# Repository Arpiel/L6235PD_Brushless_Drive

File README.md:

# L6235PD_Brushless_Drive
L6235PD BLDC Drive Project

3 Phase brushless Drive using L6235PDTR

Using Tool:KiCad 7.0

L6235 datasheet:https://www.st.com/resource/en/datasheet/l6235.pdf

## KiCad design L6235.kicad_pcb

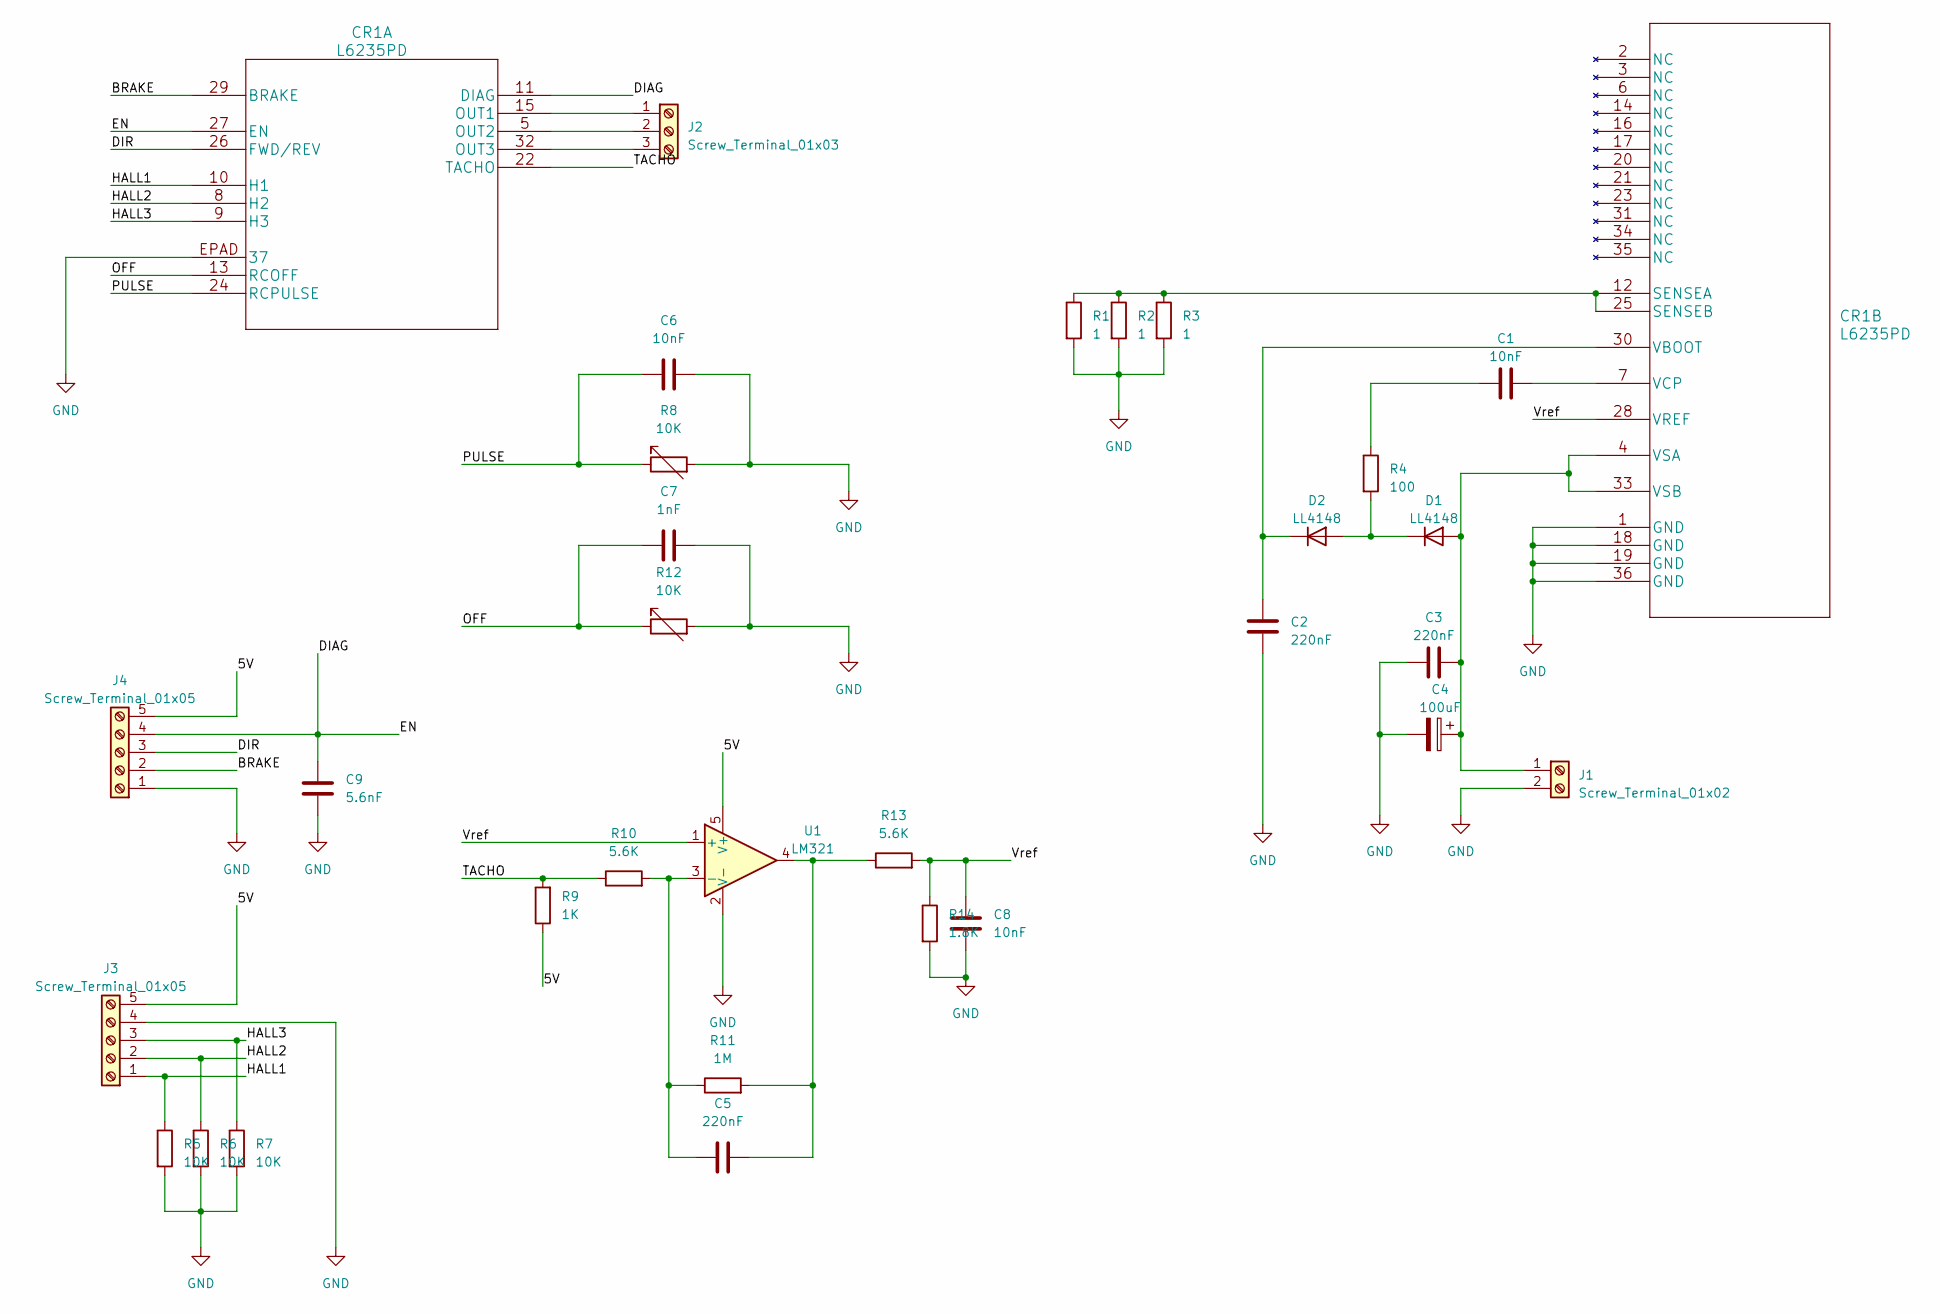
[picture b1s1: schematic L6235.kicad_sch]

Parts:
C1, C6, C8: 10nF; C_0603_1608Metric
C2, C3, C5: 220nF; C_0603_1608Metric
C4: 100uF; CP_Elec_6.3x5.3
C7: 1nF; C_0603_1608Metric
C9: 5.6nF; C_0603_1608Metric
CR1: L6235PD
D1, D2: LL4148; D_MiniMELF
J1: Screw_Terminal_01x02; TerminalBlock_RND_205-00001_1x02_P5.00mm_Horizontal
J2: Screw_Terminal_01x03; TerminalBlock_RND_205-00002_1x03_P5.00mm_Horizontal
J3, J4: Screw_Terminal_01x05; TerminalBlock_RND_205-00004_1x05_P5.00mm_Horizontal
R1, R2, R3: 1; R_2512_6332Metric
R4: 100; R_0603_1608Metric
R5, R6, R7: 10K; R_0603_1608Metric
R8, R12: 10K; Potentiometer_Vishay_T73XW_Horizontal
R9: 1K; R_0603_1608Metric
R10, R13: 5.6K; R_0603_1608Metric
R11: 1M; R_0603_1608Metric
R14: 1.8K; R_0603_1608Metric_Pad0.98x0.95mm_HandSolder
U1: LM321; SOT-23-5

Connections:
/5V: J3.5, J4.5, R8.3, R9.1, R12.3, U1.5 (V+)
/BRAKE: CR1.29 (BRAKE), J4.2
/DIAG: C9.1, CR1.11 (DIAG), CR1.27 (EN), J4.4
/DIR: CR1.26 (FWD/REV), J4.3
/HALL1: CR1.10 (H1), J3.1, R5.1
/HALL2: CR1.8 (H2), J3.2, R6.1
/HALL3: CR1.9 (H3), J3.3, R7.1
/OFF: C7.1, CR1.13 (RCOFF), R12.1
/PULSE: C6.1, CR1.24 (RCPULSE), R8.1
/TACHO: CR1.22 (TACHO), R9.2, R10.1
/Vref: C8.1, CR1.28 (VREF), R13.2, R14.1, U1.1 (+)
GND: C2.1, C3.2, C4.2, C6.2, C7.2, C8.2, C9.2, CR1.1 (GND), CR1.18 (GND), CR1.19 (GND), CR1.36 (GND), CR1.EPAD (37), J1.2, J3.4, J4.1, R1.2, R2.2, R3.2, R5.2, R6.2, R7.2, R8.2, R12.2, R14.2, U1.2 (V-)
unnamed: C1.1, R4.1
unnamed: C5.2, R11.2, R13.1, U1.4
unnamed: CR1.15 (OUT1), J2.1
unnamed: CR1.5 (OUT2), J2.2
unnamed: CR1.32 (OUT3), J2.3
unnamed: CR1.12 (SENSEA), CR1.25 (SENSEB), R1.1, R2.1, R3.1
unnamed: C2.2, CR1.30 (VBOOT), D2.1 (K)
unnamed: C1.2, CR1.7 (VCP)
unnamed: C3.1, C4.1, CR1.4 (VSA), CR1.33 (VSB), D1.2 (A), J1.1
unnamed: D1.1 (K), D2.2 (A), R4.2
unnamed: C5.1, R10.2, R11.1, U1.3 (-)

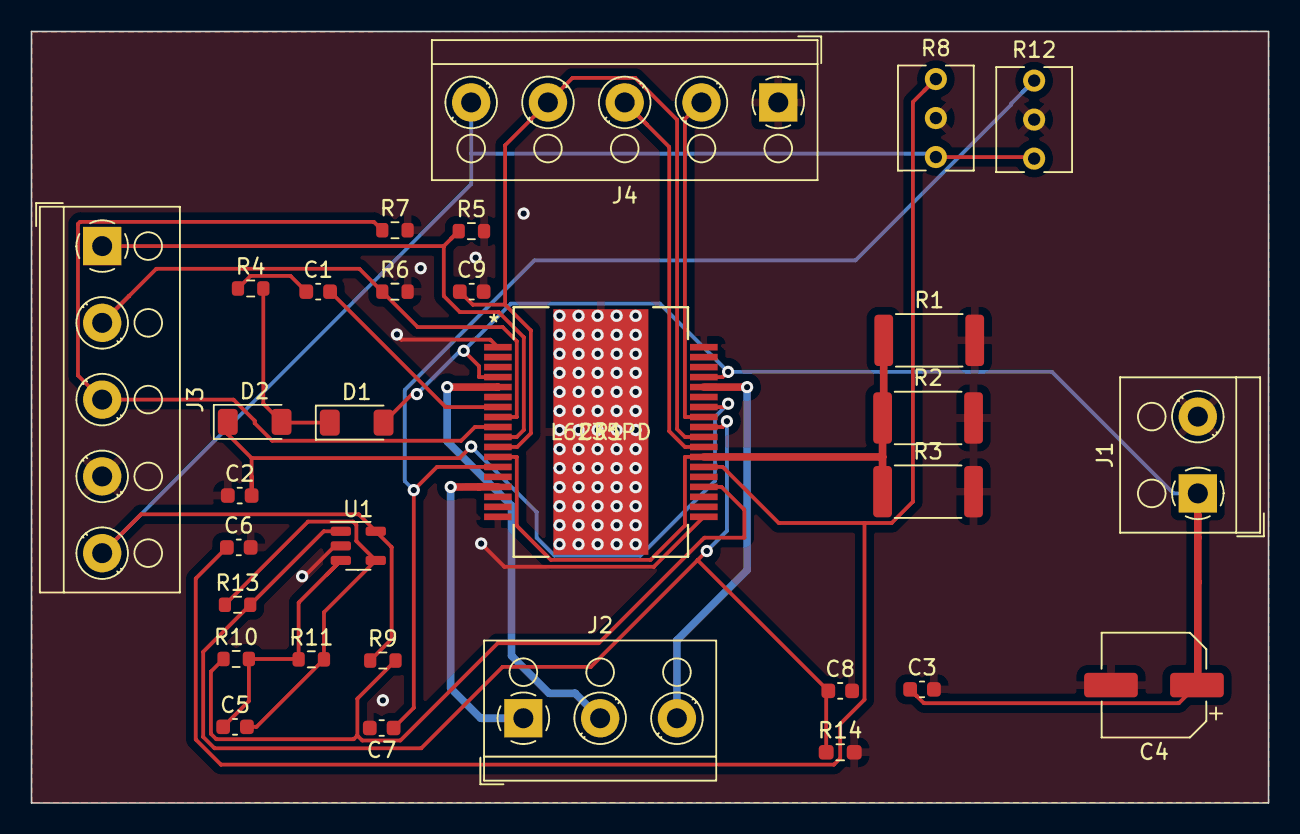
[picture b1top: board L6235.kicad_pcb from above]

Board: 2 copper layers, 80.6 x 50.2 mm, 31 parts (0 on the bottom side), 23 nets.

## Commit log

2023-08-09 첫 커밋
    첫 업데이트

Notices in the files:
parts and their libraries:
Copyright 2016 Accelerated Designs. All rights reserved.
